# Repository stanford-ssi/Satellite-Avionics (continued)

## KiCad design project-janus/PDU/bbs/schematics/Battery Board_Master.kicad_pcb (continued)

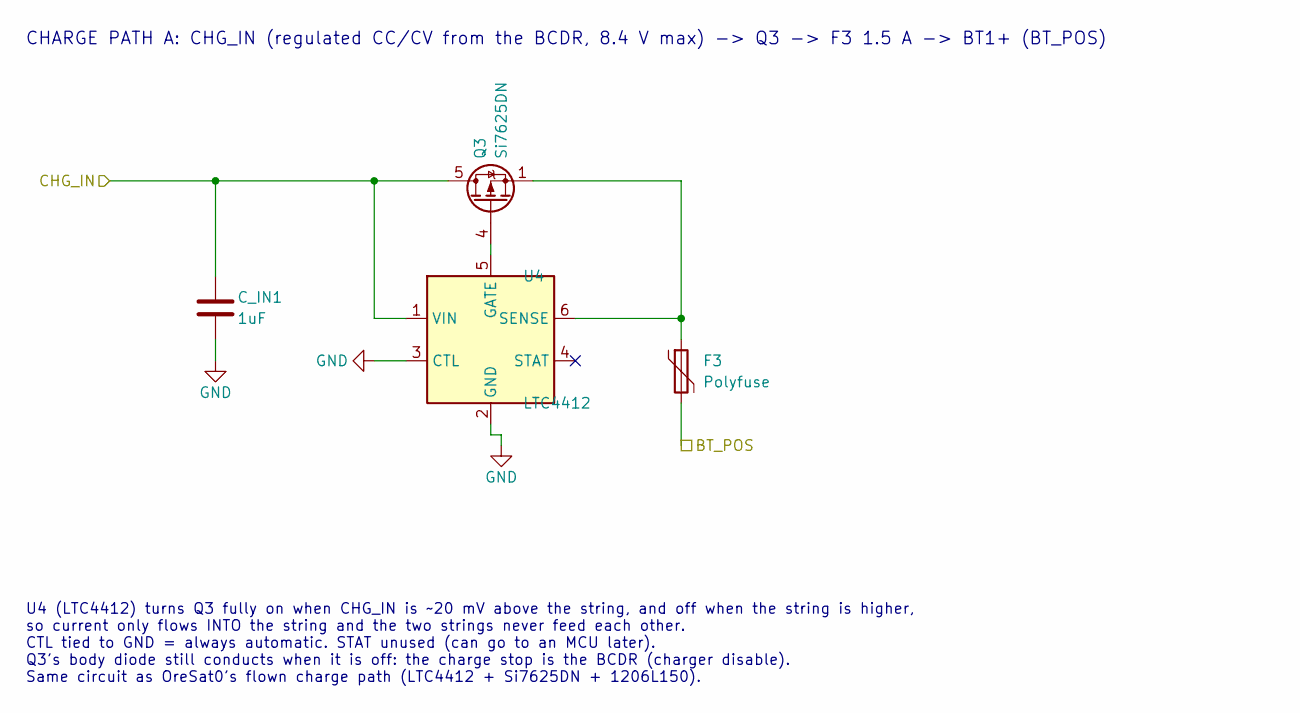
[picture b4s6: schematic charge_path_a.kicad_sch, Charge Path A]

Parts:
C_IN1: 1uF; C_0603_1608Metric; MPN CGA3E3X7R1H105K080AB
F3: Polyfuse; Fuse_1206_3216Metric; MPN 1206L150/12SLYR
Q3: Si7625DN; Vishay_PowerPAK_1212-8_Single; MPN SI7625DN-T1-GE3
U4: LTC4412; TSOT-23-6; MPN LTC4412ES6#TRPBF

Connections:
/Batteries/BT_A_POS: F3.2; also elsewhere on the board
/Charge Path A/CHG_IN: C_IN1.1, Q3.5 (D), U4.1 (VIN); also elsewhere on the board
GND: C_IN1.2, U4.2 (GND), U4.3 (CTL); also elsewhere on the board
unnamed: Q3.4 (G), U4.5 (GATE)
unnamed: F3.1, Q3.1 (S), Q3.2 (S), Q3.3 (S), U4.6 (SENSE)

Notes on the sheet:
CHARGE PATH A: CHG_IN (regulated CC/CV from the BCDR, 8.4 V max) -> Q3 -> F3 1.5 A -> BT1+ (BT_POS)
U4 (LTC4412) turns Q3 fully on when CHG_IN is ~20 mV above the string, and off when the string is higher, so current only flows INTO the string and the two strings never feed each other. CTL tied to GND = always automatic. STAT unused (can go to an MCU later). Q3's body diode still conducts when it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

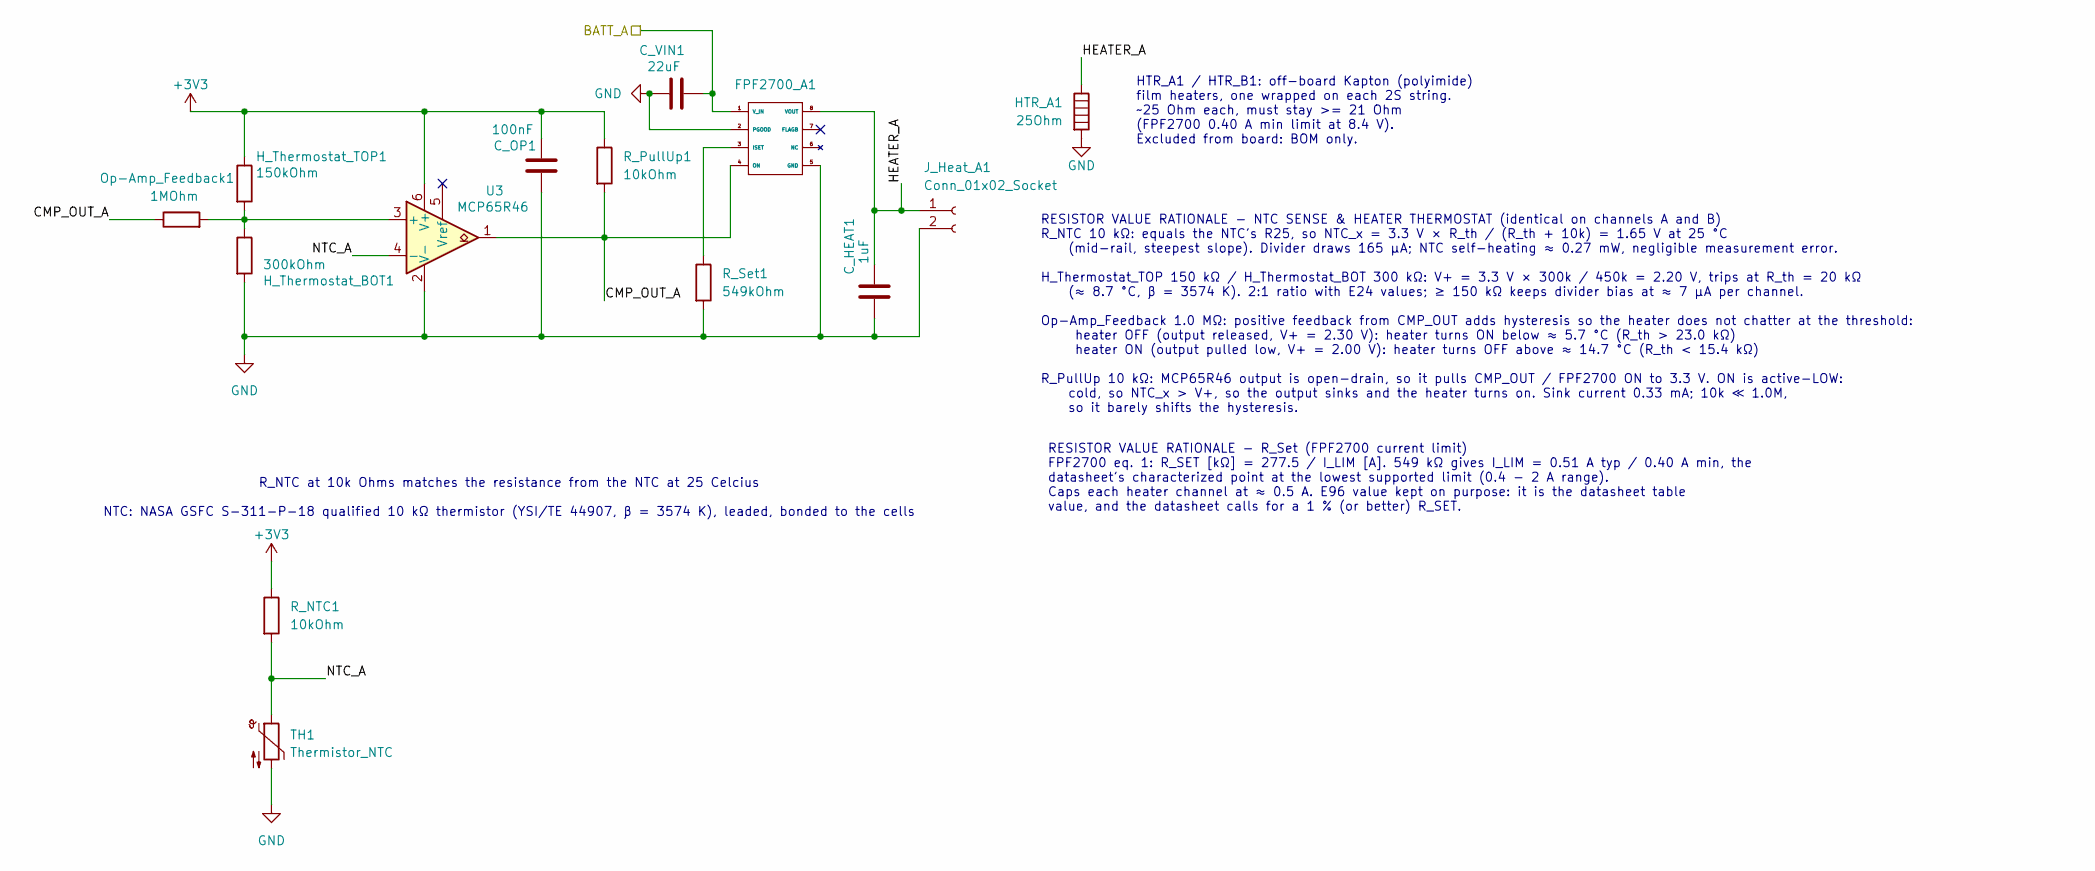
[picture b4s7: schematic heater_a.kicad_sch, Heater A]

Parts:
C_HEAT1: 1uF; C_0603_1608Metric; MPN CGA3E3X7R1H105K080AB; LCSC_PreFlight C15849
C_OP1: 100nF; C_0402_1005Metric; MPN GCM155R71H104KE02D; LCSC_PreFlight C1525
C_VIN1: 22uF; C_1206_3216Metric; MPN GRM31CC71E226ME15L; LCSC_PreFlight C12891
FPF2700_A1: SOIC-8_3.9x4.9mm_P1.27mm; MPN FPF2700MX; LCSC_PreFlight C328059
HTR_A1: 25Ohm; MPN TBD - Minco polyimide (Kapton) film hea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
H_Thermostat_BOT1: 300kOhm; R_0805_2012Metric; MPN TNPW0805300KBEEA; LCSC_PreFlight C17616
H_Thermostat_TOP1: 150kOhm; R_0805_2012Metric; MPN TNPW0805150KBEEA; LCSC_PreFlight C17470
J_Heat_A1: Conn_01x02_Socket; JST_PH_S2B-PH-SM4-TB_1x02-1MP_P2.00mm_Horizontal; MPN S2B-PH-SM4-TB(LF)(SN); LCSC_PreFlight C295747
Op-Amp_Feedback1: 1MOhm; R_0805_2012Metric; MPN TNPW08051M00BEEA; LCSC_PreFlight Verify at LCSC
R_NTC1: 10kOhm; R_0805_2012Metric; MPN TNPW080510K0BEEA; LCSC_PreFlight C17414
R_PullUp1: 10kOhm; R_0805_2012Metric; MPN TNPW080510K0BEEA; LCSC_PreFlight C17414
R_Set1: 549kOhm; R_0805_2012Metric; MPN TNPW0805549KBEEA; LCSC_PreFlight C17749
TH1: Thermistor_NTC; SolderWire-0.1sqmm_1x02_P3.6mm_D0.4mm_OD1mm; MPN 44907 (NASA GSFC S-311-P-18/07S7R6); LCSC_PreFlight N/A - DigiKey/Mouser
U3: MCP65R46; SOT-23-6; MPN MCP65R46T-1202E/CHY; LCSC_PreFlight Not stocked at LCSC - order from DigiKe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

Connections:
+3V3: C_OP1.1, H_Thermostat_TOP1.1, R_NTC1.1, R_PullUp1.1, U3.6 (V+); also elsewhere on the board
/Batteries/BATT_A: C_VIN1.2, FPF2700_A1.1 (V_IN); also elsewhere on the board
/Heater A/CMP_OUT_A: FPF2700_A1.4 (ON), Op-Amp_Feedback1.1, R_PullUp1.2, U3.1
/Heater A/HEATER_A: C_HEAT1.1, FPF2700_A1.8 (VOUT), HTR_A1.1, J_Heat_A1.1
/Heater A/NTC_A: R_NTC1.2, TH1.1, U3.4 (-)
GND: C_HEAT1.2, C_OP1.2, C_VIN1.1, FPF2700_A1.2 (PGOOD), FPF2700_A1.5 (GND), HTR_A1.2, H_Thermostat_BOT1.2, J_Heat_A1.2, R_Set1.2, TH1.2, U3.2 (V-); also elsewhere on the board
unnamed: FPF2700_A1.3 (ISET), R_Set1.1
unnamed: H_Thermostat_BOT1.1, H_Thermostat_TOP1.2, Op-Amp_Feedback1.2, U3.3 (+)

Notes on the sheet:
R_NTC at 10k Ohms matches the resistance from the NTC at 25 Celcius NTC: NASA GSFC S-311-P-18 qualified 10 kΩ thermistor (YSI/TE 44907, β = 3574 K), leaded, bonded to the cells
RESISTOR VALUE RATIONALE - R_Set (FPF2700 current limit) FPF2700 eq. 1: R_SET [kΩ] = 277.5 / I_LIM [A]. 549 kΩ gives I_LIM = 0.51 A typ / 0.40 A min, the datasheet's characterized point at the lowest supported limit (0.4 - 2 A range). Caps each heater channel at ≈ 0.5 A. E96 value kept on purpose: 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
RESISTOR VALUE RATIONALE - NTC SENSE & HEATER THERMOSTAT (identical on channels A and B) R_NTC 10 kΩ: equals the NTC's R25, so NTC_x = 3.3 V × R_th / (R_th + 10k) = 1.65 V at 25 °C (mid-rail, steepest slope). Divider draws 165 µA; NTC self-heating ≈ 0.27 mW, negligible measurement error. H_Thermost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
HTR_A1 / HTR_B1: off-board Kapton (polyimide) film heaters, one wrapped on each 2S string. ~25 Ohm each, must stay >= 21 Ohm (FPF2700 0.40 A min limit at 8.4 V). Excluded from board: BOM only.

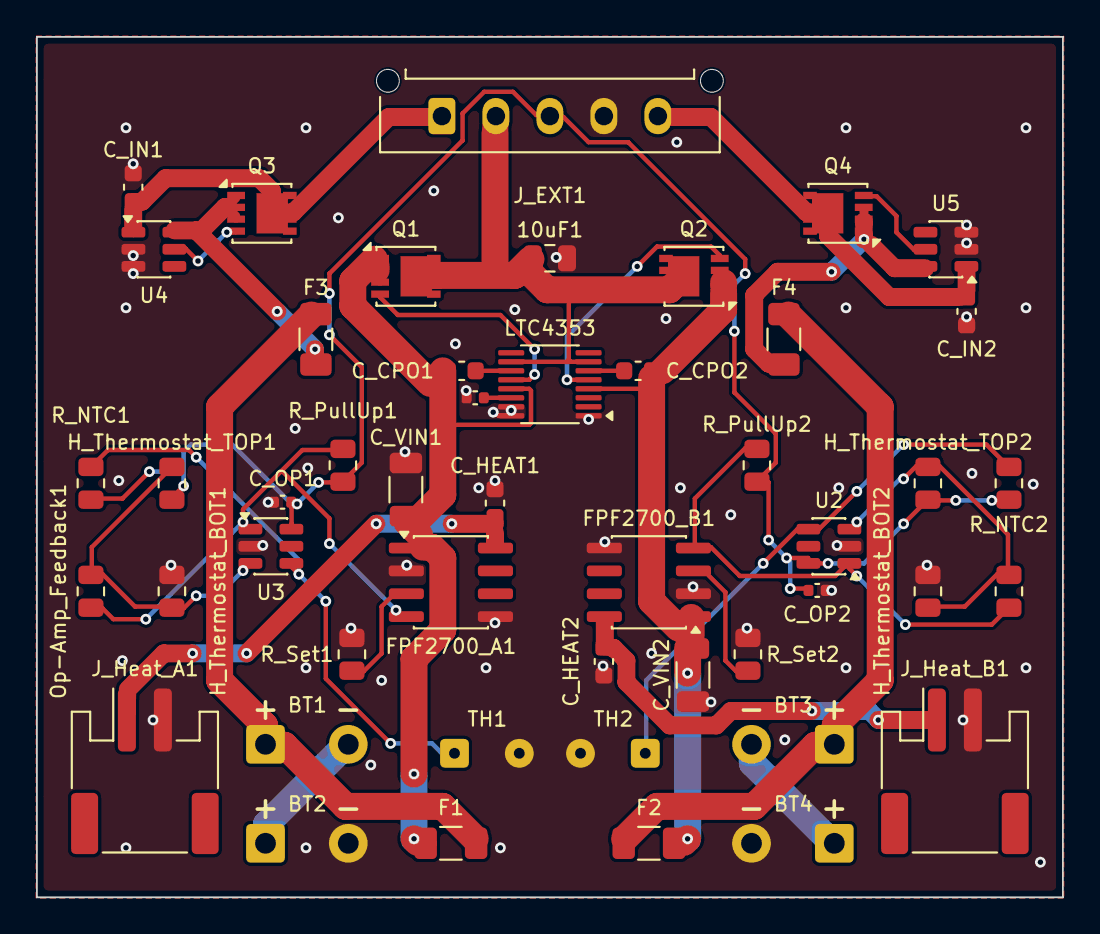
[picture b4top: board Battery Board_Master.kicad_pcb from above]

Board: 2 copper layers, 57.0 x 47.8 mm, 48 parts (0 on the bottom side), 30 nets.
